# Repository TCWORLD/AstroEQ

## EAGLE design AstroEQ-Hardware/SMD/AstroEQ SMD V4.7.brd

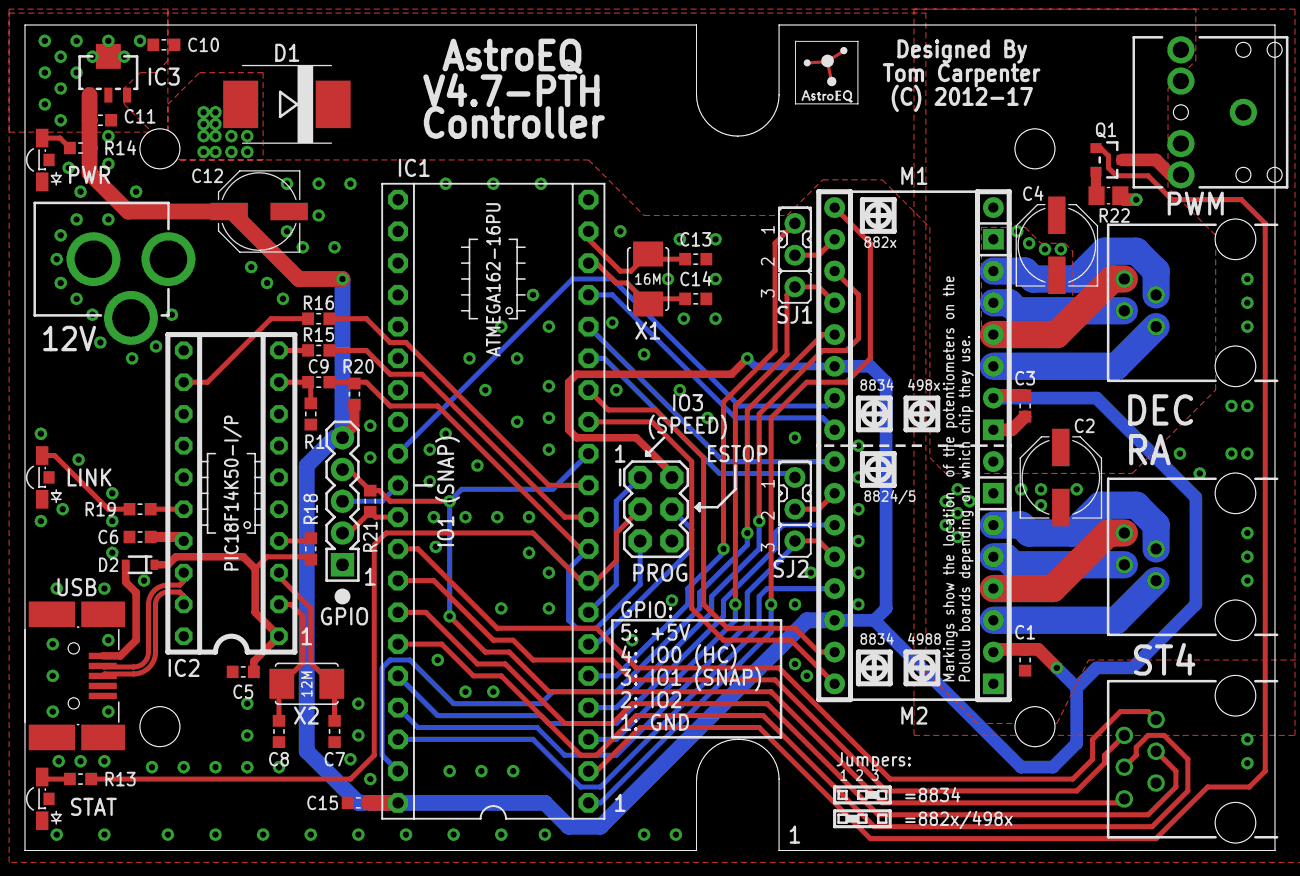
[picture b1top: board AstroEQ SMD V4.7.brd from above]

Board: 2 copper layers, 100.0 x 66.0 mm, 54 parts (0 on the bottom side), 61 nets.

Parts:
12V: POWER_JACKPTH; POWER_JACK_PTH
C1, C3, C5, C9, C10, C11, C15: 100n; C0603
C2, C4, C12: 100u; PANASONIC_D
C6: 470n; C0603
C7, C8, C13, C14: 22p; C0603
D1: B550C-13; SMC
D2: RB511VM-30FHTE-17; SOD-323
DEC: RJ11-4-LP; RJ11-NO_SHIELD-4-LP
GPIO: DNI; 1X05
HAMMOND-1593N: HAMMOND-1593N-4HOLE; HAMMOND-1593N4HOLES
IC1: DIP40-SOCKET; DIL40
IC2: DIP20-SOCKET; DIL20-SKT
IC3: 78L05; SOT89
ICL1: ATMEGA162-16PU; IC
ICL2: PIC18F14K50-I/P; IC
J2, J3: DNI; JUMP
LINK: Red; SML1206-SIDE
LOGO1: DNI; ASTROEQ-SMALL
M1: Motor Driver; CARRIER-HV-DUAL
M2: Motor Driver; CARRIER-LV-DUAL
PROG: AVR_PRG; 2X3
PWM: JACK; AUDIO-JACK
PWR: Red; SML1206-SIDE
Q1: NTR4501NT1G; SOT23-3
R1, R18, R20: 10k; R0603
R13, R14, R15, R16, R19, R21: 1k; R0603
R22: 120; R0805
RA: RJ11-4-LP; RJ11-NO_SHIELD-4-LP
SJ1, SJ2: 3pin HDR; JP2
ST4: RJ11-6; RJ11-NO_SHIELD-LP
STAT: Red; SML1206-SIDE
USB: Molex 67803-8020; USB-MINIAB
X1: 16MHz; NX5032
X2: 12MHz; NX5032

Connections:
!EN-1: IC1.1, M2.1_1
!EN-2: IC1.16, M2.1_2
!RST-1: IC1.39, M2.5_1
!RST-2: IC1.38, M2.5_2
+5V: C1.1, C3.1, C11.1, C12.+, C15.1, GPIO.5, IC1.40, IC3.1, M1.10_1, M1.10_2, M2.6_1, M2.6_2, PROG.2, R14.1, R20.2
AVROSC1: C13.1, IC1.19, X1.P$2
AVROSC2: C14.1, IC1.18, X1.P$1
DEC+/SI: IC1.33, ST4.5
DEC-1A: DEC.5, M1.12_1
DEC-1B: DEC.2, M1.11_1
DEC-2A: DEC.3, M1.13_1
DEC-2B: DEC.4, M1.14_1
DEC-/CK: IC1.34, ST4.4
DIR-1: IC1.17, M2.8_1
DIR-2: IC1.13, M2.8_2
DTR: C9.1, IC2.9, R1.1
D_N: IC2.18, USB.D-
D_P: IC2.19, USB.D+
ESTOP-MOSI: IC1.6, PROG.4
GND: 12V.GND, 12V.GNDBREAK, C1.2, C2.-, C3.2, C4.-, C5.2, C6.1, C7.2, C8.2, C10.2, C11.2, C12.-, C13.2, C14.2, C15.2, GPIO.1, IC1.20, IC2.20, IC3.2, IC3.4, LINK.C, LINK.E, M1.9_1, M1.9_2, M1.15_1, M1.15_2, PROG.6, PWM.SLEEVE, PWR.C, PWR.E, R1.2, R22.1, ST4.2, STAT.C, STAT.E, USB.GND, USB.GND1, USB.GND2, USB.GND3, USB.GND4
IO0: GPIO.4, IC1.12, R21.1, ST4.1
IO1: GPIO.3, IC1.30
IO2: GPIO.2, IC1.31, R21.2
IO3-MISO: IC1.7, PROG.1
MCLR: IC2.4, R18.1
MS1-1: IC1.5, SJ1.1
MS1-2: IC1.15, SJ2.1
MS2-1: IC1.4, M2.3_1
MS2-2: IC1.36, M2.3_2
MS3-1: IC1.3, M2.4_1, SJ1.3
MS3-2: IC1.37, M2.4_2, SJ2.3
MS13-1: M2.2_1, SJ1.2
MS13-2: M2.2_2, SJ2.2
PWM: IC1.2, Q1.1
PWM-ILIM: Q1.2, R22.2
PWM-OD: PWM.RING, Q1.3
PWRLED: PWR.A, R14.2
RA+/SO: IC1.32, ST4.6
RA-1A: M1.12_2, RA.5
RA-1B: M1.11_2, RA.2
RA-2A: M1.13_2, RA.3
RA-2B: M1.14_2, RA.4
RA-/!SS: IC1.35, ST4.3
RESET: C9.2, IC1.9, PROG.5, R20.1
RX: IC1.11, R16.1
RX(USB): IC2.12, R16.2
STAT-SCLK: IC1.8, PROG.3, R13.1
STATLED: R13.2, STAT.A
STEP-1: IC1.29, M2.7_1
STEP-2: IC1.14, M2.7_2
TX: IC1.10, R15.1
TX(USB): IC2.10, R15.2
USBLED: LINK.A, R19.1
USBOSC1: C8.1, IC2.2, X2.P$2
USBOSC2: C7.1, IC2.3, X2.P$1
USBSTAT: IC2.16, R19.2
V+: C2.+, C4.+, C10.1, D1.C, IC3.3, M1.16_1, M1.16_2, PWM.TIP
VBUS: D2.2, USB.VBUS
VIN: 12V.PWR, D1.A
VPIC: C5.1, D2.1, IC2.1, R18.2
VUSB: C6.2, IC2.17

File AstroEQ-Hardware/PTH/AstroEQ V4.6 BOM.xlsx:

Qty | Parts | Value | Description | Manufacturer | Part Number | Farnell Code
2 | SJ1, SJ2 | - | Solder Jumper - See PCB for details | - | - | -
7 | C1, C3, C5, C9, C10, C11, C15 | 100nF | 100nF Ceramic Capacitor, 50V, 2.54mm pitch | MULTICOMP | MCRR25104X7RK0050 | 1216438
3 | C2, C4, C12 | 100uF | 100uF Alu Electrolytic Capacitor, 25V, Dia 6.3mm | MULTICOMP | MCGPR25V107M6.3X11 | 9451188
4 | C7, C8, C13, C14 | 22pF | 22pF Ceramic Capacitor, 2.54mm pitch | AVX | SR151A220JAR | 1100369
1 | D1 | MBR1060 | TO-220 Schottky Diode, 10A | MULTICOMP | MBR1060 | 1625119
1 | ST4 | RJ11-6 | RJ11 JACK, 6/6 LOW PROFILE | MOLEX | 95501-2661 | 1536490
2 | DEC, RA | RJ11-4 | RJ11 JACK, 6/4 LOW PROFILE | MOLEX | 95501-2641 | 1560166
1 | HAMMOND-1593N | HAMMOND-1593N | CASE, ABS, HANDHELD, BLACK, 111X75X25MM | HAMMOND | 1593NBK | 9287566
1 | IC1 | ATMEGA162-16PU | IC, ATMEGA162-16PU, DIP40 | ATMEL | ATMEGA162-16PU | 9171169
1 | IC1 | DIP40 Socket | 40Way DIP IC Socket, 0.3" Pitch | MULTICOMP | 2227-20-03-07 | 4285608
1 | IC2 | PIC18F14K50-I/P | IC, PIC18F14K50-I/P, PDIP20 | MICROCHIP | PIC18F14K50-I/P | 1648501
1 | IC2 | DIP20 Socket | 40Way DIP IC Socket, 0.6" Pitch | MULTICOMP | 2227-40-06-05 | 4285669
1 | IC3 | 78L05 | 5V 100mA Voltage Regulator, TO-92 | FAIRCHILD SEMICONDUCTOR | LM78L05ACZX | 1467367
1 | J1 | MJ-179PH | DC Barrel Jack Socket, PCB Mount | MULTICOMP | MJ-179PH | 1737246
2 | M1, M2 | Motor Driver Socket | RECEPTACLE, 2.54MM, SINGLE, 16WAY | SAMTEC | CES-116-01-T-S | 1667522
1 | PROG | 2x3 Header | 2ROW, 6WAY, 2.54mm Pitch Header | TE CONNECTIVITY / AMP | 826632-3 | 3418492
6 | R13, R14, R15, R16, R19, R21 | 1kR | 1k Resistor, 1/4W, 5% | MULTICOMP | MF12 1K | 9342400
1 | USB-> | Mini USB Connector | MINI USB RECEPTACLE, THT, R/A | MOLEX | 565790519 | 1125347
1 | X2 | 12MHz XTAL | XTAL, 12.000MHZ, 18PF, HC-49S | TXC | 9B-12.000MAAJ-B | 1842203
3 | R1, R18, R20 | 10kR | 10k Resistor, 1/4W, 5% | MULTICOMP | MF12 10K | 9342419
3 | PWR, STAT, USB | 3mm LED Red | Flat Top Red LED, 3mm | KINGBRIGHT | L-424HDT | 1142499
1 | X1 | 16MHz XTAL | XTAL, 16.000MHZ, 18PF, HC-49S | TXC | 9B-16.000MEEJ-B | 1842217
1 | D2 | 1N4148 | DIODE, 100V,150MA, DO-35 | MULTICOMP | 1N4148 | 9565124
1 | C6 | 470nF | 470nF Ceramic Capacitor, 50V, 2.54mm pitch | KEMET | C320C474M5U5TA | 1457660
1 | R22 | 120R | 120R Resistor, 1/4W, 5% | MULTICOMP | MF12 120R | 9342516
1 | Q1 | BS270 | MOSFET TRANSISTOR, N CHANNEL, BS270 | FAIRCHILD SEMICONDUCTOR | BS270 | 1017689
1 | PWM | 3.5mm JACK | PHONE AUDIO CONNECTOR, JACK, 3.5MM | CLIFF ELECTRONIC COMPONENETS | FC68131 | 2518188
1 Pack | - | Mounting PCB to Case | WASHER, FLAT, NYLON, M2.5, PK50 | DURATOOL | 110764 | 7047472
1 Pack | - | Mounting PCB to Case | SCREW, POZI PAN, STEEL, BZP, M2.5X6 | TR FASTENINGS | M2.56 PRSTTTZ100 | 1420119

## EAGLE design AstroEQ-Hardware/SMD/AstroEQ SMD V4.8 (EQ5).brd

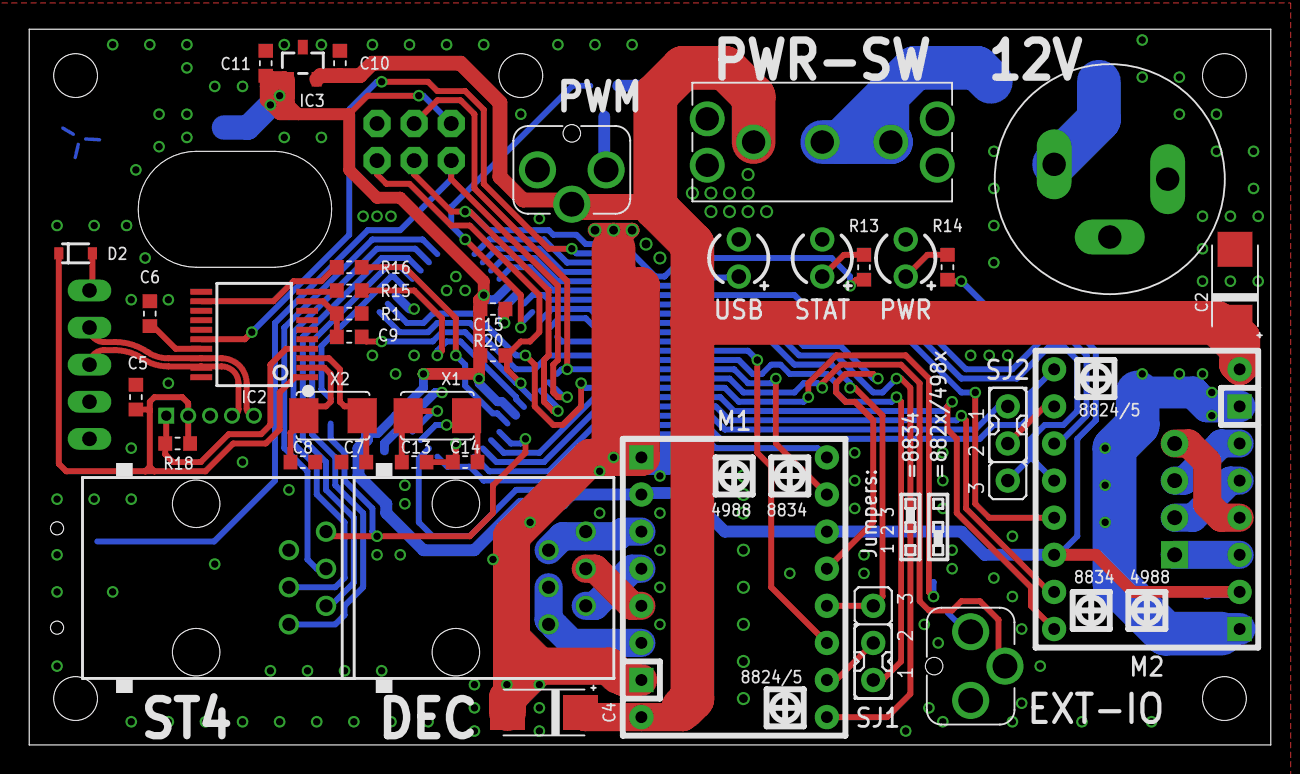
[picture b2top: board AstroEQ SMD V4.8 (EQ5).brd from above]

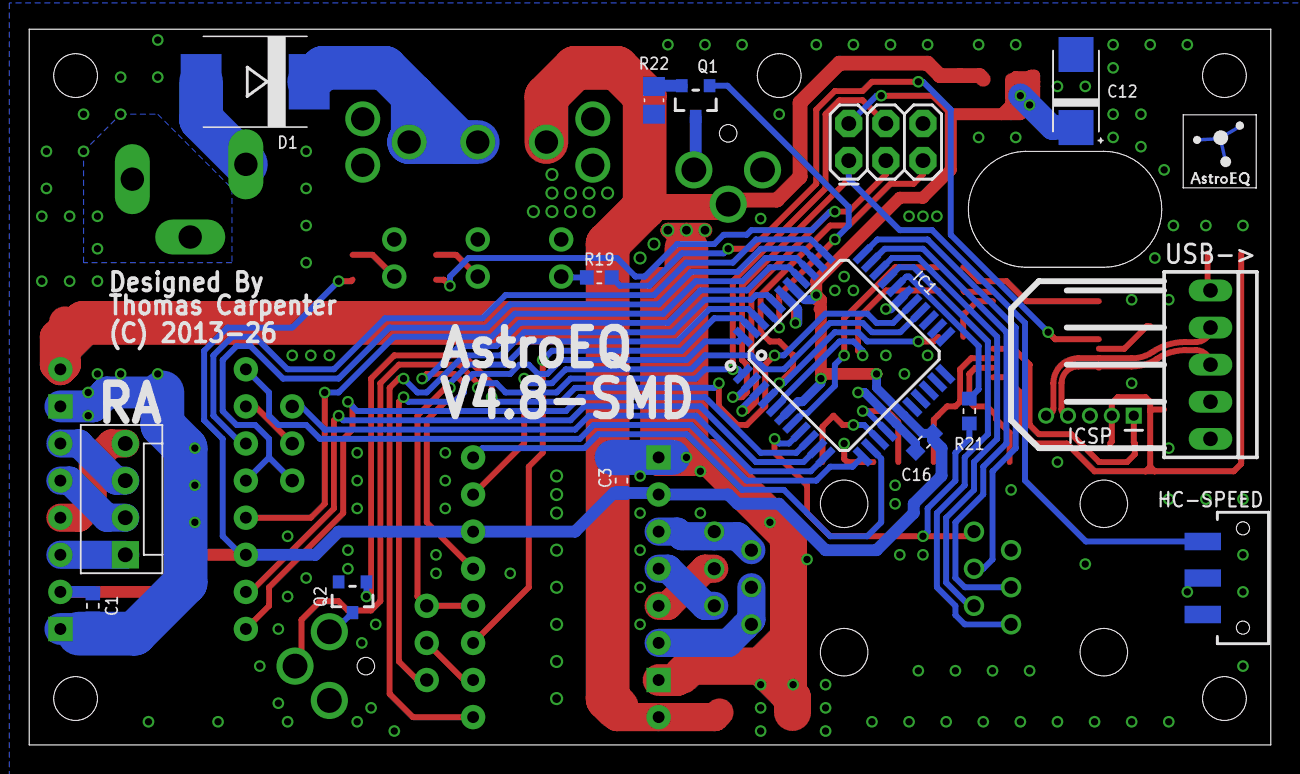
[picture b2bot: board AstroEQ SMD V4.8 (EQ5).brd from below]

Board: 2 copper layers, 85.0 x 49.0 mm, 56 parts (17 on the bottom side), 63 nets.

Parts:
C1, C3, C5, C9, C10, C11, C15, C16: 100n; C0603
C2, C4: 33u; SMC_C
C6: 470n; C0603
C7, C8, C13, C14: 22p; C0603
C12: 68u; SMC_C
D1: B550C-13; SMC
D2: RB511VM-30FHTE-17; SOD-323
DEC: RJ11-6; RJ11-NO_SHIELD
EXT-IO: JACK; AUDIO-JACK-3.5MM-VERT
HC-SPEED: JS102011SAQN; SWITCH-SPDT-SMD
IC1: ATMEGA162-16AU; TQFP44
IC2: PIC18F14K50-I/SS; SS20
IC3: 78L05; SOT23
ICSP: PIC-ICSP-MINI
J1: POWER_JACKPANEL; POWER_JACK_PANEL
J2, J3: DNI; JUMP
JP1: MC34645; MOLEX-1X4
LOGO1: ASTROEQ5MM; ASTROEQ-SMALL
M1, M2: Motor Driver; DIP16-W
PROG: AVR_PRG; 2X3
PWM: JACK; AUDIO-JACK-3.5MM-VERT
PWR: Red; LED3MM
PWR-SW: SWITCH; SPST
Q1, Q2: NTR4501NT1G; SOT23-3
R1, R18, R20: 10k; R0603
R13, R14, R15, R16, R19, R21: 1k; R0603
R22: 120; R0805
SJ1, SJ2: 2211S-03G; JP2
ST4: RJ11-6; RJ11-NO_SHIELD
STAT: Red; LED3MM
USB: Red; LED3MM
USB->: MC34649; 22-23-2051
X1: 16MHz; NX5032
X2: 12MHz; NX5032

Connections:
!EN-1: IC1.40, M1.1
!EN-2: IC1.12, M2.1
!RST-1: IC1.37, M1.5
!RST-2: IC1.36, M2.5
+5V: C1.1, C3.1, C11.1, C12.+, C15.1, C16.1, IC1.6, IC1.17, IC1.38, IC3.1, M1.6, M1.10, M2.6, M2.10, PROG.2, R14.1, R20.2
AVROSC1: C13.1, IC1.15, X1.P$1
AVROSC2: C14.1, IC1.14, X1.P$2
DEC+/SI: IC1.31, ST4.5
DEC-1A: DEC.5, M1.12
DEC-1B: DEC.1, DEC.2, M1.11
DEC-2A: DEC.3, M1.13
DEC-2B: DEC.4, DEC.6, M1.14
DEC-/CK: IC1.32, ST4.4
DIR-1: IC1.13, M1.8
DIR-2: IC1.9, M2.8
DTR: C9.1, IC2.9, R1.1
D_N: IC2.18, ICSP.5, USB->.2
D_P: IC2.19, ICSP.4, USB->.3
ESTOP-MOSI: EXT-IO.2, IC1.1, PROG.4
GND: C1.2, C2.-, C3.2, C4.-, C5.2, C6.1, C7.2, C8.2, C10.2, C11.2, C12.-, C13.2, C14.2, C15.2, C16.2, EXT-IO.1, HC-SPEED.2, HC-SPEED.3, IC1.16, IC1.28, IC1.39, IC2.20, IC3.3, ICSP.3, J1.SHUNT, J1.SLEEVE, M1.9, M1.15, M2.9, M2.15, PROG.6, PWM.1, PWR.K, PWR-SW.S1, PWR-SW.S2, PWR-SW.S3, PWR-SW.S4, Q2.2, R1.2, R22.1, ST4.2, STAT.K, USB.K, USB->.4, USB->.5
IO0: IC1.8, R21.1, ST4.1
IO1: IC1.27, Q2.1
IO1-OD: EXT-IO.3, Q2.3
IO2: IC1.29, R21.2
IO3-MISO: HC-SPEED.1, IC1.2, PROG.1
MCLR: IC2.4, ICSP.1, R18.1
MS1-1: IC1.44, SJ1.1
MS1-2: IC1.11, SJ2.1
MS2-1: IC1.43, M1.3
MS2-2: IC1.34, M2.3
MS3-1: IC1.42, M1.4, SJ1.3
MS3-2: IC1.35, M2.4, SJ2.3
MS13-1: M1.2, SJ1.2
MS13-2: M2.2, SJ2.2
PWM: IC1.41, Q1.1
PWM-OD: PWM.3, Q1.3
PWM-RES: Q1.2, R22.2
PWRLED: PWR.A, R14.2
RA+/SO: IC1.30, ST4.6
RA-1A: JP1.4, M2.12
RA-1B: JP1.1, M2.11
RA-2A: JP1.2, M2.13
RA-2B: JP1.3, M2.14
RA-/!SS: IC1.33, ST4.3
RESET: C9.2, IC1.4, PROG.5, R20.1
RX: IC1.7, R16.1
RX(USB): IC2.12, R16.2
STAT-SCLK: IC1.3, PROG.3, R13.1
STATLED: R13.2, STAT.A
STEP-1: IC1.26, M1.7
STEP-2: IC1.10, M2.7
SWITCH: D1.C, PWR-SW.COM, PWR-SW.NO
TX: IC1.5, R15.1
TX(USB): IC2.10, R15.2
USBLED: R19.1, USB.A
USBOSC1: C8.1, IC2.2, X2.P$2
USBOSC2: C7.1, IC2.3, X2.P$1
USBSTAT: IC2.16, R19.2
V+: C2.+, C4.+, C10.1, IC3.2, M1.16, M2.16, PWM.2, PWR-SW.NC
VBUS: D2.2, USB->.1
VIN: D1.A, J1.CENTRE
VPIC: C5.1, D2.1, IC2.1, ICSP.2, R18.2
VUSB: C6.2, IC2.17

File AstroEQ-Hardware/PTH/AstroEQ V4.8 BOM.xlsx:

Qty | Parts | Value | Description | Manufacturer | Part Number | Farnell Code
2 | SJ1, SJ2 | - | Solder Jumper - See PCB for details | - | - | -
7 | C1, C3, C5, C9, C10, C11, C15 | 100nF | 100nF Ceramic Capacitor, 50V, 2.54mm pitch | MULTICOMP | MCRR25104X7RK0050 | 1216438
3 | C2, C4, C12 | 100uF | 100uF Alu Electrolytic Capacitor, 25V, Dia 6.3mm | MULTICOMP | MCGPR25V107M6.3X11 | 9451188
4 | C7, C8, C13, C14 | 22pF | 22pF Ceramic Capacitor, 2.54mm pitch | AVX | SR151A220JAR | 1100369
1 | D1 | MBR1060 | TO-220 Schottky Diode, 10A | MULTICOMP | MBR1060 | 1625119
1 | ST4 | RJ11-6 | RJ11 JACK, 6/6 LOW PROFILE | MOLEX | 95501-2661 | 1536490
2 | DEC, RA | RJ11-4 | RJ11 JACK, 6/4 LOW PROFILE | MOLEX | 95501-2641 | 1560166
1 | HAMMOND-1593N | HAMMOND-1593N | CASE, ABS, HANDHELD, BLACK, 111X75X25MM | HAMMOND | 1593NBK | 9287566
1 | IC1 | ATMEGA162-16PU | IC, ATMEGA162-16PU, DIP40 | ATMEL | ATMEGA162-16PU | 9171169
1 | IC1 | DIP40 Socket | 40Way DIP IC Socket, 0.3" Pitch | MULTICOMP | 2227-20-03-07 | 4285608
1 | IC2 | PIC18F14K50-I/P | IC, PIC18F14K50-I/P, PDIP20 | MICROCHIP | PIC18F14K50-I/P | 1648501
1 | IC2 | DIP20 Socket | 40Way DIP IC Socket, 0.6" Pitch | MULTICOMP | 2227-40-06-05 | 4285669
1 | IC3 | 78L05 | 5V 100mA Voltage Regulator, TO-92 | FAIRCHILD SEMICONDUCTOR | LM78L05ACZX | 1467367
1 | J1 | MJ-179PH | DC Barrel Jack Socket, PCB Mount | MULTICOMP | MJ-179PH | 1737246
2 | M1, M2 | Motor Driver Socket | RECEPTACLE, 2.54MM, SINGLE, 16WAY | SAMTEC | CES-116-01-T-S | 1667522
1 | PROG | 2x3 Header | 2ROW, 6WAY, 2.54mm Pitch Header | TE CONNECTIVITY / AMP | 826632-3 | 3418492
7 | R13, R14, R15, R16, R19, R21, R23 | 1kR | 1k Resistor, 1/4W, 5% | MULTICOMP | MF12 1K | 9342400
1 | USB-> | Mini USB Connector | MINI USB RECEPTACLE, THT, R/A | MOLEX | 565790519 | 1125347
1 | X2 | 12MHz XTAL | XTAL, 12.000MHZ, 18PF, HC-49S | TXC | 9B-12.000MAAJ-B | 1842203
3 | R1, R18, R20 | 10kR | 10k Resistor, 1/4W, 5% | MULTICOMP | MF12 10K | 9342419
3 | PWR, STAT, USB | 3mm LED Red | Flat Top Red LED, 3mm | KINGBRIGHT | L-424HDT | 1142499
1 | X1 | 16MHz XTAL | XTAL, 16.000MHZ, 18PF, HC-49S | TXC | 9B-16.000MEEJ-B | 1842217
1 | D2 | 1N4148 | DIODE, 100V,150MA, DO-35 | MULTICOMP | 1N4148 | 9565124
1 | C6 | 470nF | 470nF Ceramic Capacitor, 50V, 2.54mm pitch | KEMET | C320C474M5U5TA | 1457660
1 | R22 | 120R | 120R Resistor, 1/4W, 5% | MULTICOMP | MF12 120R | 9342516
1 | Q1 | BS270 | MOSFET TRANSISTOR, N CHANNEL, BS270 | FAIRCHILD SEMICONDUCTOR | BS270 | 1017689
1 | PWM | 3.5mm JACK | PHONE AUDIO CONNECTOR, JACK, 3.5MM | CLIFF ELECTRONIC COMPONENETS | FC68131 | 2518188
1 Pack | - | Mounting PCB to Case | WASHER, FLAT, NYLON, M2.5, PK50 | DURATOOL | 110764 | 7047472
1 Pack | - | Mounting PCB to Case | SCREW, POZI PAN, STEEL, BZP, M2.5X6 | TR FASTENINGS | M2.56 PRSTTTZ100 | 1420119

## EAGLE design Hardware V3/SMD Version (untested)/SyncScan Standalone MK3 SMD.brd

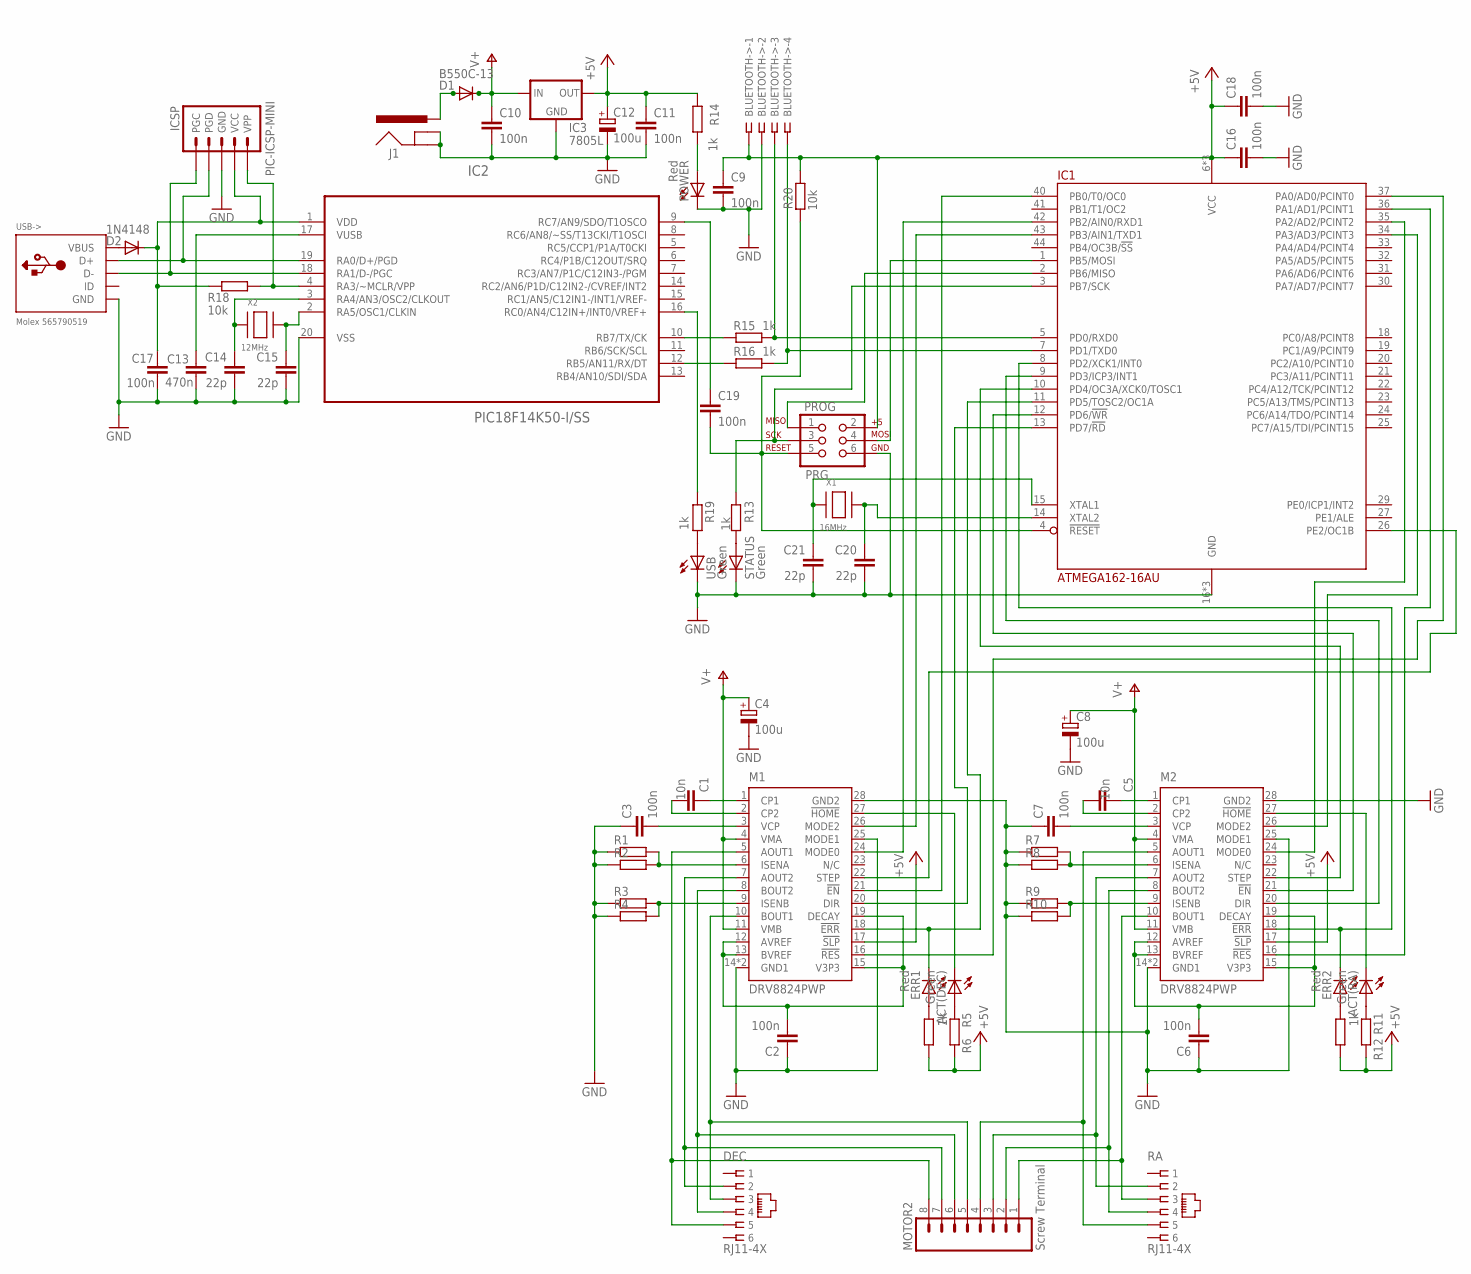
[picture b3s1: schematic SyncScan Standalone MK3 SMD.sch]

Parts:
ACT(DEC): Green; 1206; MPN L-424GDT
ACT(RA): Green; 1206; MPN L-424GDT
BLUETOOTH->: http://www.ebay.co.uk/itm/250991624201; SSW-104-02-S-S-RA
C1, C5: 10n; C0603K; MPN C0603C103K1RACTU
C2, C3, C6, C7, C9, C10, C11, C16, C17, C18, C19: 100n; C0603K; MPN C0603C104K4RACTU
C4, C8, C12: 100u; E2,5-6; MPN MCGPR25V107M6.3X11
C13: 470n; C0603K; MPN 0603ZD474KAT2A
C14, C15, C20, C21: 22p; C0603K; MPN U0603C220JCT
D1: B550C-13; SMC; MPN B550C-13-F
D2: 1N4148; SOD-323; MPN 1N4148.
DEC: RJ11-4X; RJ11-NO_SHIELD; MPN MHRJJ64NFRA
ERR1, ERR2: Red; 1206; MPN L-424HDT
IC1: ATMEGA162-16AU; TQFP44; MPN ATMEGA162-16AU
IC2: PIC18F14K50-I/SS; SSOP20; MPN PIC18F14K50-I/SS
IC3: 7805L; SOT23; MPN TS78L05CX RF
ICSP: PIC-ICSP-MINI
J1: POWER_JACKSMD; POWER_JACK_SMD; MPN MJ-179SMT
M1, M2: DRV8824PWP; HTSSOP28PWP; MPN DRV8824PWP
MOTOR2: Screw Terminal; SCREWTERMINAL-3.5MM-8; MPN KRMC 08
POWER: Red; 1206; MPN L-424HDT
PROG: PRG; 2X3; MPN 826632-3
R1, R2, R3, R4, R7, R8, R9, R10: 1.5R; R2512; MPN RC2512FK-7W1R5L
R5, R6, R11, R12, R13, R14, R15, R16, R19: 1k; R0603; MPN CRCW06031K00FKEA
R18, R20: 10k; R0603; MPN CRCW060310K0FKEA
RA: RJ11-4X; RJ11-NO_SHIELD; MPN MHRJJ64NFRA
STATUS: Green; 1206; MPN L-424GDT
USB: Green; 1206; MPN L-424GDT
USB->: Molex 565790519; USB-MINIB-THM-MOLEX; MPN 565790519
X1: 16MHz; NX5032; MPN 7A-16.000MAAJ-T
X2: 12MHz; NX5032; MPN 7A-12.000MAAJ-T

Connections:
3.3V-1: C2.2, M1.12 (AVREF), M1.13 (BVREF), M1.15 (V3P3), M1.19 (DECAY)
3.3V-2: C6.2, M2.12 (AVREF), M2.13 (BVREF), M2.15 (V3P3), M2.19 (DECAY)
!EN-1: IC1.40 (PB0/T0/OC0), M1.21 (!EN)
!EN-2: IC1.12 (PD6/!WR), M2.21 (!EN)
!ERR-1: ERR1.C, IC1.11 (PD5/TOSC2/OC1A), M1.18 (!ERR)
!ERR-2: ERR2.C, IC1.8 (PD2/XCK1/INT0), M2.18 (!ERR)
!HOME-1: ACT(DEC).C, M1.27 (!HOME)
!HOME-2: ACT(RA).C, M2.27 (!HOME)
!RST-1: IC1.37 (PA0/AD0/PCINT0), M1.16 (!RES)
!RST-2: IC1.36 (PA1/AD1/PCINT1), M2.16 (!RES)
+5V: BLUETOOTH->.1, C9.1, C11.1, C12.+, C16.1, C18.1, IC1.6 (VCC), IC1.17 (VCC), IC1.38 (VCC), IC3.1 (OUT), M1.17 (!SLP), M2.17 (!SLP), PROG.2, R5.2, R6.2, R11.2, R12.2, R14.1, R20.2
A1-1: DEC.5, M1.5 (AOUT1), MOTOR2.8
A1-2: M2.5 (AOUT1), MOTOR2.4, RA.5
A2-1: DEC.2, M1.7 (AOUT2), MOTOR2.7
A2-2: M2.7 (AOUT2), MOTOR2.3, RA.2
AVROSC1: C21.1, IC1.15 (XTAL1), X1.P$1
AVROSC2: C20.1, IC1.14 (XTAL2), X1.P$2
B1-1: DEC.3, M1.10 (BOUT1), MOTOR2.5
B1-2: M2.10 (BOUT1), MOTOR2.1, RA.3
B2-1: DEC.4, M1.8 (BOUT2), MOTOR2.6
B2-2: M2.8 (BOUT2), MOTOR2.2, RA.4
CP1-1: C1.1, M1.1 (CP1)
CP1-2: C5.1, M2.1 (CP1)
CP2-1: C1.2, M1.2 (CP2)
CP2-2: C5.2, M2.2 (CP2)
D+: IC2.19 (RA0/D+/PGD), ICSP.4 (PGD), USB->.D+
D-: IC2.18 (RA1/D-/PGC), ICSP.5 (PGC), USB->.D-
DIR-1: IC1.13 (PD7/!RD), M1.20 (DIR)
DIR-2: IC1.9 (PD3/ICP3/INT1), M2.20 (DIR)
GND: BLUETOOTH->.2, C2.1, C3.1, C4.-, C6.1, C7.1, C8.-, C9.2, C10.2, C11.2, C12.-, C13.1, C14.2, C15.2, C16.2, C17.2, C18.2, C20.2, C21.2, IC1.16 (GND), IC1.28 (GND), IC1.39 (GND), IC2.20 (VSS), IC3.3 (GND), ICSP.3 (GND), J1.GND (GNDBREAK), J1.P$4 (GND), M1.14 (GND1), M1.25 (MODE1), M1.28 (GND2), M1.EXP (GND1), M2.14 (GND1), M2.25 (MODE1), M2.28 (GND2), M2.EXP (GND1), POWER.C, PROG.6, R1.1, R2.1, R3.1, R4.1, R7.1, R8.1, R9.1, R10.1, STATUS.C, USB.C, USB->.GND
ISENA-1: M1.6 (ISENA), R1.2, R2.2
ISENA-2: M2.6 (ISENA), R7.2, R8.2
ISENB-1: M1.9 (ISENB), R3.2, R4.2
ISENB-2: M2.9 (ISENB), R9.2, R10.2
LED1: ERR1.A, R6.1
LED2: ACT(DEC).A, R5.1
LED3: ERR2.A, R12.1
LED4: ACT(RA).A, R11.1
M0-1: IC1.42 (PB2/AIN0/RXD1), M1.24 (MODE0)
M0-2: IC1.35 (PA2/AD2/PCINT2), M2.24 (MODE0)
M2-1: IC1.43 (PB3/AIN1/TXD1), M1.26 (MODE2)
M2-2: IC1.34 (PA3/AD3/PCINT3), M2.26 (MODE2)
MCLR: IC2.4 (RA3/~MCLR/VPP), ICSP.1 (VPP), R18.1
MISO: IC1.2 (PB6/MISO), PROG.1
MOSI: IC1.1 (PB5/MOSI), PROG.4
unnamed: C3.2, M1.3 (VCP)
unnamed: C19.1, IC2.9 (RC7/AN9/SDO/T1OSCO)
PWRLED: POWER.A, R14.2
RESET: C19.2, IC1.4 (!RESET), PROG.5, R20.1
RX(BTH): BLUETOOTH->.4, IC1.7 (PD1/TXD0), R16.1
RX(USB): IC2.12 (RB5/AN11/RX/DT), R16.2
SCLK: IC1.3 (PB7/SCK), PROG.3, R13.1
STATLED: R13.2, STATUS.A
STEP-1: IC1.26 (PE2/OC1B), M1.22 (STEP)
STEP-2: IC1.10 (PD4/OC3A/XCK0/TOSC1), M2.22 (STEP)
TX(BTH): BLUETOOTH->.3, IC1.5 (PD0/RXD0), R15.1
TX(USB): IC2.10 (RB7/TX/CK), R15.2
USBLED: R19.1, USB.A
USBOSC1: C15.1, IC2.2 (RA5/OSC1/CLKIN), X2.P$2
USBOSC2: C14.1, IC2.3 (RA4/AN3/OSC2/CLKOUT), X2.P$1
USBSTAT: IC2.16 (RC0/AN4/C12IN+/INT0/VREF+), R19.2
V+: C4.+, C8.+, C10.1, D1.C, IC3.2 (IN), M1.4 (VMA), M1.11 (VMB), M2.4 (VMA), M2.11 (VMB)
VBUS: D2.2 (A), USB->.VBUS
VCP-2: C7.2, M2.3 (VCP)
VIN: D1.A, J1.VIN0 (PWR), J1.VIN1 (PWR)
VPIC: C17.1, D2.1 (C), IC2.1 (VDD), ICSP.2 (VCC), R18.2
VUSB: C13.2, IC2.17 (VUSB)

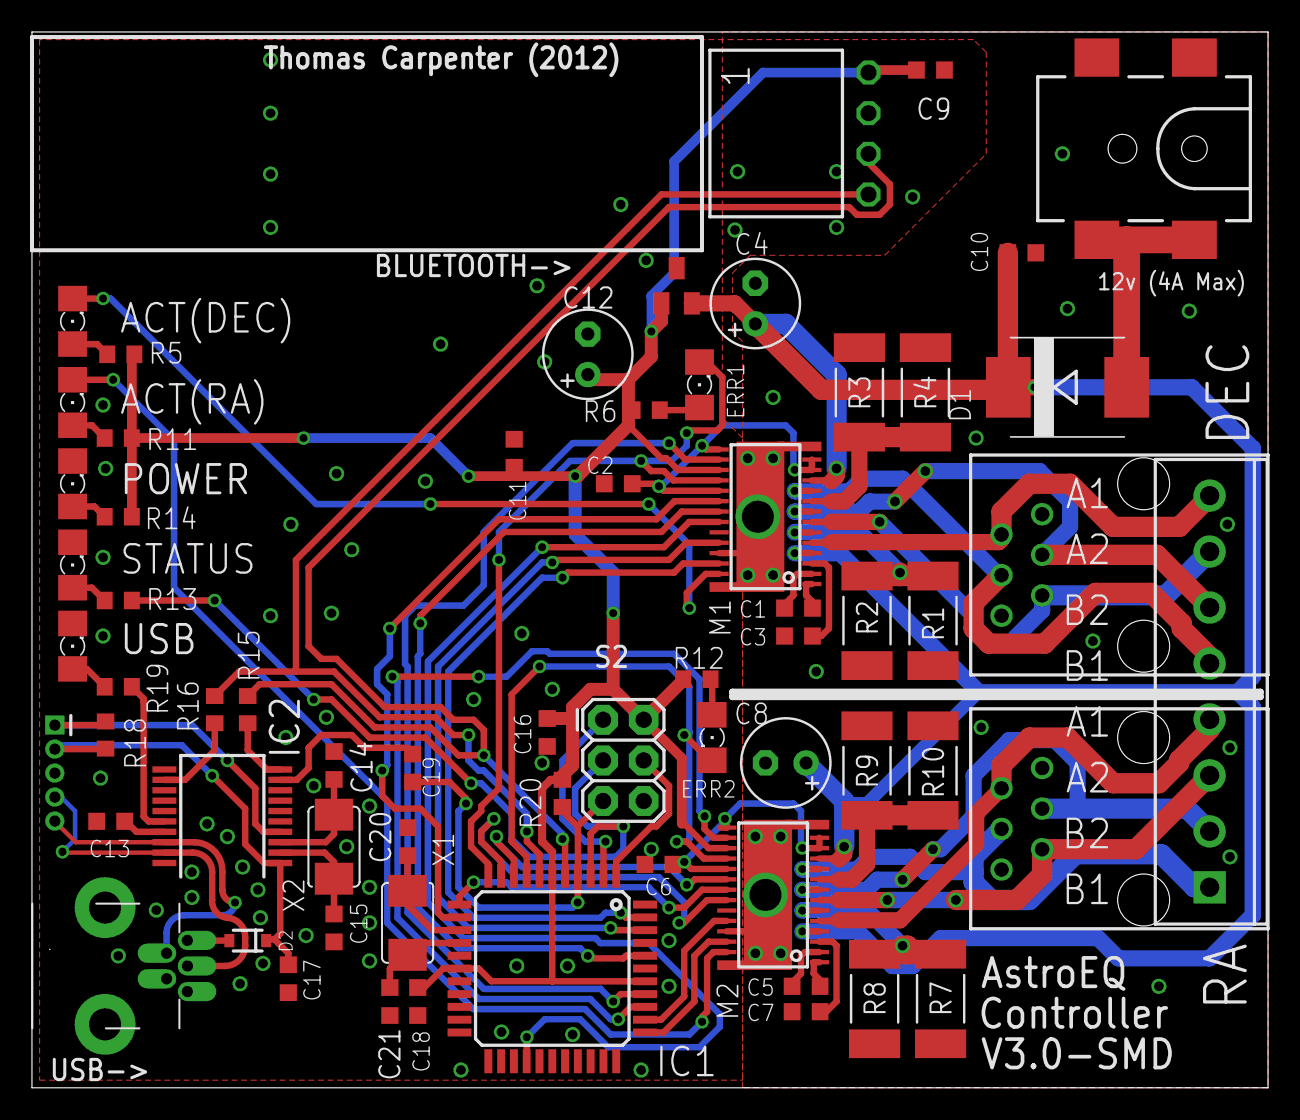
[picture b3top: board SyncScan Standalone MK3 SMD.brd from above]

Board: 2 copper layers, 77.3 x 66.0 mm, 64 parts (0 on the bottom side), 67 nets.

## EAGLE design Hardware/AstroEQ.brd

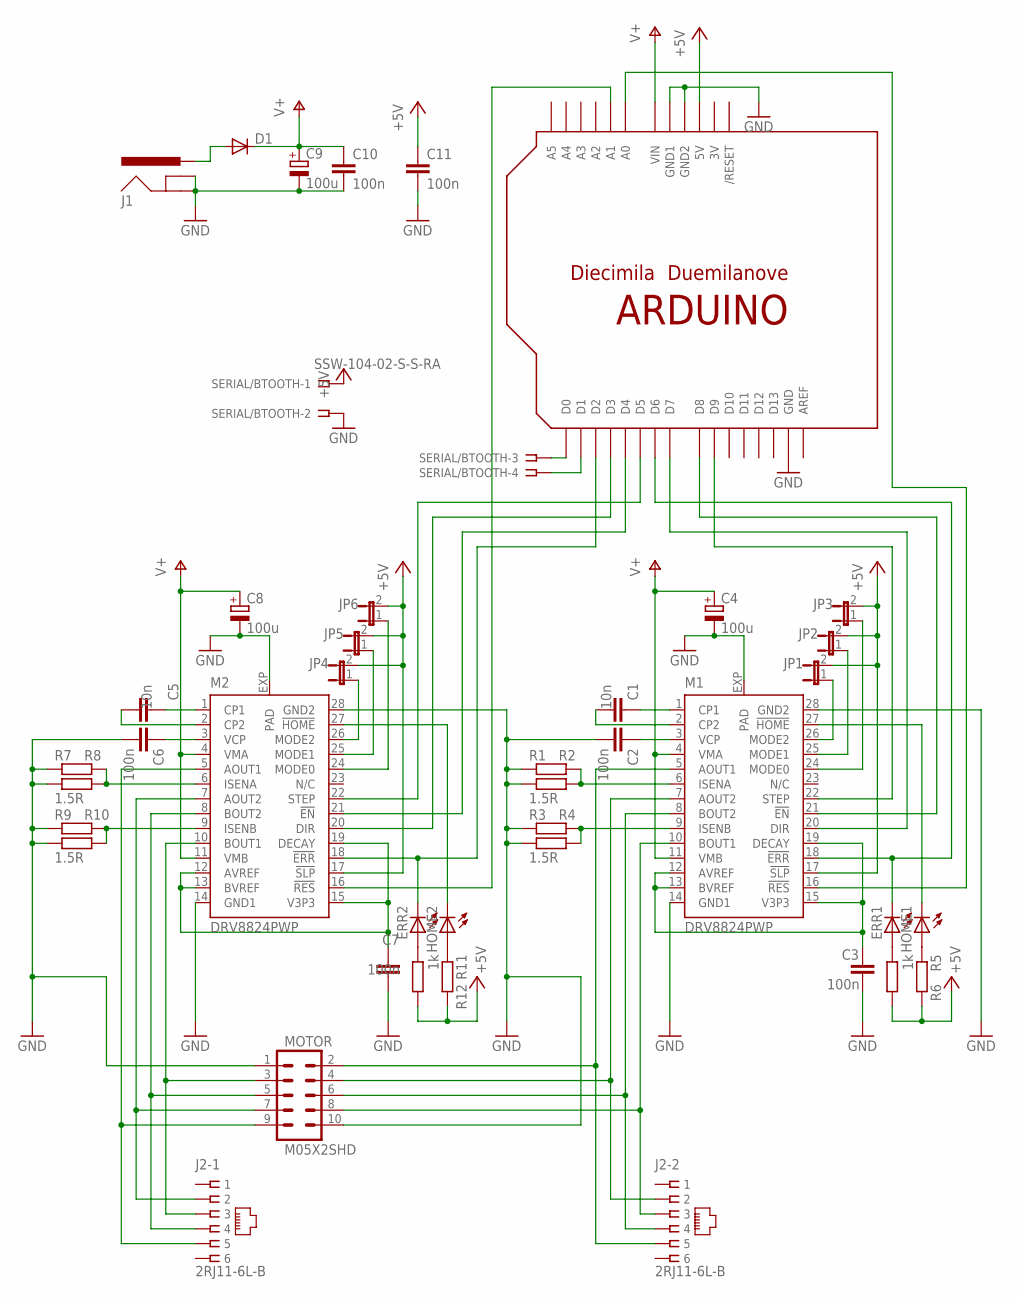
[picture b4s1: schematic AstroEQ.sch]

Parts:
C1, C5: 10n; C0603K
C2, C3, C6, C7, C10, C11: 100n; C0603K
C4, C8, C9: 100u; C/6032-28R
D1: DIODESMA-ALT; SMA-DIODE_ALT
ERR1, ERR2: LEDCHIP-LED0603; CHIP-LED0603
HOME1, HOME2: LEDCHIP-LED0603; CHIP-LED0603
J1: POWER_JACKPTH; POWER_JACK_PTH
J2: 2RJ11-6L-B; 2RJ11
JP1, JP2, JP3, JP4, JP5, JP6: JUMPER-2SMD-NO; SJ_2S-NO
M1, M2: DRV8824PWP; HTSSOP28PWP
MOTOR: M05X2SHD; 2X5-SHROUDED
R1, R2, R3, R4, R7, R8, R9, R10: 1.5R; R2512
R5, R6, R11, R12: 1k; R0603
SERIAL/BTOOTH: SSW-104-02-S-S-RA
U$1: ARDUINOUNO; ARDUINO

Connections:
3.3V-1: C3.1, M1.12 (AVREF), M1.13 (BVREF), M1.15 (V3P3), M1.19 (DECAY)
3.3V-2: C7.1, M2.12 (AVREF), M2.13 (BVREF), M2.15 (V3P3), M2.19 (DECAY)
3V: U$1.3V
!EN-1: M1.21 (!EN), U$1.D8
!EN-2: M2.21 (!EN), U$1.D4
!ERR-1: M1.16 (!RES), U$1.A0
!ERR-2: ERR2.C, M2.18 (!ERR), U$1.D2
!HOME-1: HOME1.C, M1.27 (!HOME)
!HOME-2: HOME2.C, M2.27 (!HOME)
!RST-1: ERR1.C, M1.18 (!ERR), U$1.D6
!RST-2: M2.16 (!RES), U$1.A1
+5V: C11.1, JP1.2, JP2.2, JP3.2, JP4.2, JP5.2, JP6.2, M1.17 (!SLP), M2.17 (!SLP), R5.2, R6.2, R11.2, R12.2, SERIAL/BTOOTH.1, U$1.5V
A1-1: J2.2-5 (5), M1.5 (AOUT1), MOTOR.2
A1-2: J2.1-5 (5), M2.5 (AOUT1), MOTOR.9
A2-1: J2.2-2 (2), M1.7 (AOUT2), MOTOR.4
A2-2: J2.1-2 (2), M2.7 (AOUT2), MOTOR.7
B1-1: J2.2-3 (3), M1.10 (BOUT1), MOTOR.8
B1-2: J2.1-3 (3), M2.10 (BOUT1), MOTOR.3
B2-1: J2.2-4 (4), M1.8 (BOUT2), MOTOR.6
B2-2: J2.1-4 (4), M2.8 (BOUT2), MOTOR.5
CP1-1: C1.1, M1.1 (CP1)
CP1-2: C5.1, M2.1 (CP1)
CP2-1: C1.2, M1.2 (CP2)
CP2-2: C5.2, M2.2 (CP2)
DIR-1: M1.20 (DIR), U$1.D7
DIR-2: M2.20 (DIR), U$1.D3
GND: C2.2, C3.2, C4.-, C6.2, C7.2, C8.-, C9.-, C10.2, C11.2, J1.GND, J1.GNDBREAK, M1.14 (GND1), M1.28 (GND2), M1.EXP (PAD), M2.14 (GND1), M2.28 (GND2), M2.EXP (PAD), MOTOR.1, MOTOR.10, R1.1, R2.1, R3.1, R4.1, R7.1, R8.1, R9.1, R10.1, SERIAL/BTOOTH.2, U$1.GND, U$1.GND1, U$1.GND2
ISENA-1: M1.6 (ISENA), R1.2, R2.2
ISENA-2: M2.6 (ISENA), R7.2, R8.2
ISENB-1: M1.9 (ISENB), R3.2, R4.2
ISENB-2: M2.9 (ISENB), R9.2, R10.2
LED1: ERR1.A, R6.1
LED2: HOME1.A, R5.1
LED3: ERR2.A, R12.1
LED4: HOME2.A, R11.1
M0-1: JP3.1, M1.24 (MODE0)
M0-2: JP6.1, M2.24 (MODE0)
M1-1: JP2.1, M1.25 (MODE1)
M1-2: JP5.1, M2.25 (MODE1)
M2-1: JP1.1, M1.26 (MODE2)
M2-2: JP4.1, M2.26 (MODE2)
unnamed: D1.A, J1.PWR
RX: SERIAL/BTOOTH.3, U$1.D0
STEP-1: M1.22 (STEP), U$1.D9
STEP-2: M2.22 (STEP), U$1.D5
TX: SERIAL/BTOOTH.4, U$1.D1
V+: C4.+, C8.+, C9.+, C10.1, D1.C, M1.4 (VMA), M1.11 (VMB), M2.4 (VMA), M2.11 (VMB), U$1.VIN
VCP-1: C2.1, M1.3 (VCP)
VCP-2: C6.1, M2.3 (VCP)

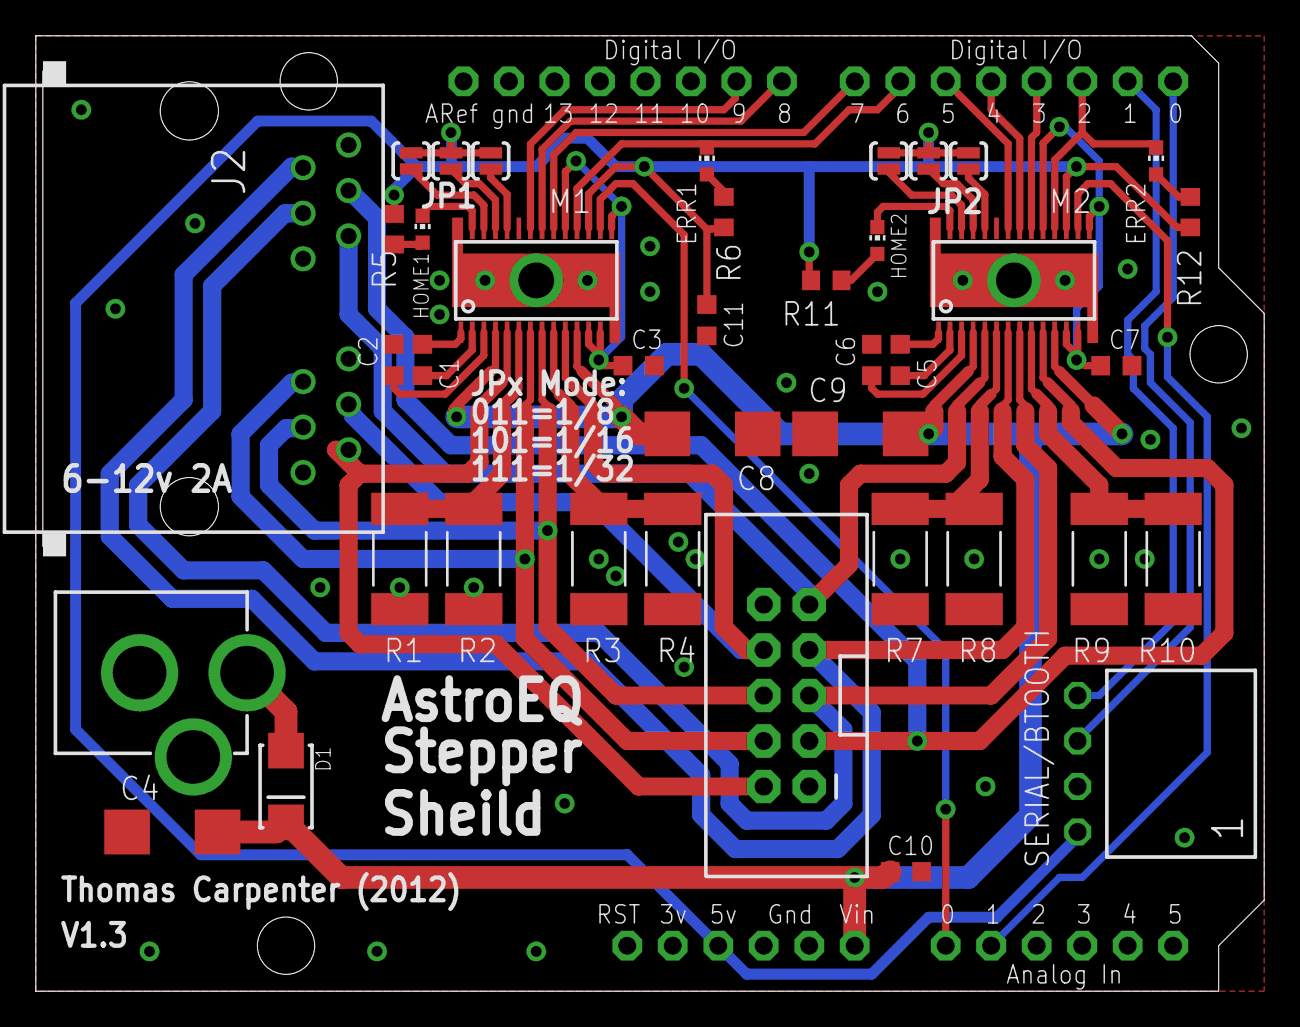
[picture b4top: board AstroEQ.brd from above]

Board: 2 copper layers, 68.6 x 53.3 mm, 41 parts (0 on the bottom side), 48 nets.

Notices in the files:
AstroEQ-Hardware/SMD/AstroEQ SMD V4.7.brd:
(C) 2012-17
AstroEQ-Hardware/SMD/AstroEQ SMD V4.8 (EQ5).brd:
(C) 2013-26
parts and their libraries:
SparkFun: Licensing: CC v3.0 Share-Alike You are welcome to use this library for commercial purposes.
